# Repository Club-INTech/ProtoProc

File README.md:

# ProtoProc #

## Equipe: ##
- Dédé Belnet
- Martial Costantini
- Pierre-François Gimenez

# Projet: #
Concevoir et construire une console de jeu avec des portes logiques.

## Etapes ##
- concevoir un processeur RISC
- le réaliser électroniquement
- écrire un assembleur
- écrire un compilateur (?)
- écrire un jeu
- intégrer des éléments extérieurs (écran, manette)
- jouer

## Constituant d'un processeur ##
- ALU (unité arithmétique et logique)
- Register file
- Séquenceur
- Horloge
- Contrôleur mémoire
- Contrôleur d'interruption
- MMU

A se répartir.

## Eléments à choisir ##
- Combien de bits? (bits effectivement utilisés + bits de redondance)
- Quels adressages disponibles?
- Jeu d'instruction? (voir plus bas)
- Mode idle?
- Timer? Compteur?

### Proposition ###
- 3 bits (données)
- 8 registres accessibles: ACC1, ACC2, SP (accessible?), flags (zero, sign, carry) (accessible?), index high, index low, E/S 1 (ou seulement entrée), E/S 2 (ou seulement sortie). Registre nul? (utile pour comparaison à zéro et initialisation)
- adressage sur 15 bits immédiats (cf largeur du bus de la mémoire ram de RS)
- adresse sur 15 bits immédiats + 6 bits provenant des deux registres d'index (une adresse du genre 1400 + INDEX)

## Matériel utilisé ##
- transistor
- portes logiques
- décodeur ?
- bascule ?
- (dé)multiplexeur ?
- eeprom ? (mémoire programme et microcode) (utiliser communication parallèle: http://fr.rs-online.com/web/p/memoires-eeprom/0394504/)
- ram ? (mémoire données et mémoire de la carte graphique. Y'a pas de SDRAM traversant chez RS mais y'a du SRAM: http://fr.rs-online.com/web/p/memoires-sram/0538148/)

L'avantage avec un processeur lent, c'est que les temps d'accès mémoire se font en un tic d'horloge...

## Jeu d'instructions ##
Si on veut un jeu rapide, il ne faut pas se contenter de quelques instructions mais ajouter des instructions assez haut niveau.
Il y a deux sortes d'instructions: les câblés (inaltérables) et les micro-codés (programmable).
Les câblés sont plus rapides que les micro-codés, mais consomment beaucoup de portes logiques.

### Instructions câblée monocycle ###
- mov
- Instructions logiques et arithmétiques sur deux registres
- Saut conditionnel (se base sur les flags)
- Saut inconditionnel
- load/store
- nop

### Instructions microcodées à voir selon le jeu. ###
- Pile ? (push, pop, call, ret)
- load/store avec index?
- Echange du contenu de deux registres ?
- Comparaison suivi d'un saut ?
- Instructions sur des booléens ?
- Instructions mémoire-registre ?
- Une instruction de nop'ification qui permettrait de supprimer des branches et de faciliter le travail du pipeline.

Exemple, au lieu de:

```
#!Assembleur

    cmp A, 0
    jz Label1 // (saute si A == 0)
    mov B, 3
    mov A, 6
    jmp Label2
Label1:
    mov B, 9
    mov C, 4
Label2:
```

On aurait:

```
#!Assembleur

    cmp A, 0
    nopz 3 // (si A == 0, ignore les trois prochaines instructions)
    mov B, 3
    mov A, 6
    nop 2  // (ignore les deux prochaines instructions)
    mov B, 9
    mov C, 4
```

On perd du temps (les instructions ignorées durent un cycle chacune) mais cela retire en embranchement. Pour les branchements pour lesquels la nopification est impossible (label en arrière ou trop de code à noper), je rappelle qu'il faut toujours ajouter des nops après le branchement afin de ne pas exécuter les instructions en aval.

```
#!Assembleur

    cmp A, 0
    jz Label1 // saute si A == 0
    nop
    nop
    nop
    (ABWABWA)
Label1:
    (ABWABWABWABWAAAA)
```

## Idées ##
- Un jeu d'instruction dynamique (qui change sans que le processeur ne s'éteigne)
- Il faudrait en plus du processeur et de sa mémoire, une carte son (pour jouer de la musique avec un floppy) et une carte graphique (qui transmet les informations de la mémoire à la matrice de led). Les fréquences de ces trois systèmes ne sont pas forcément les mêmes.
- La carte graphique pourrait gérer une matrice de diode pour les images et des afficheurs 7 segments pour les nombres. Voire utiliser un petit écran LCD.

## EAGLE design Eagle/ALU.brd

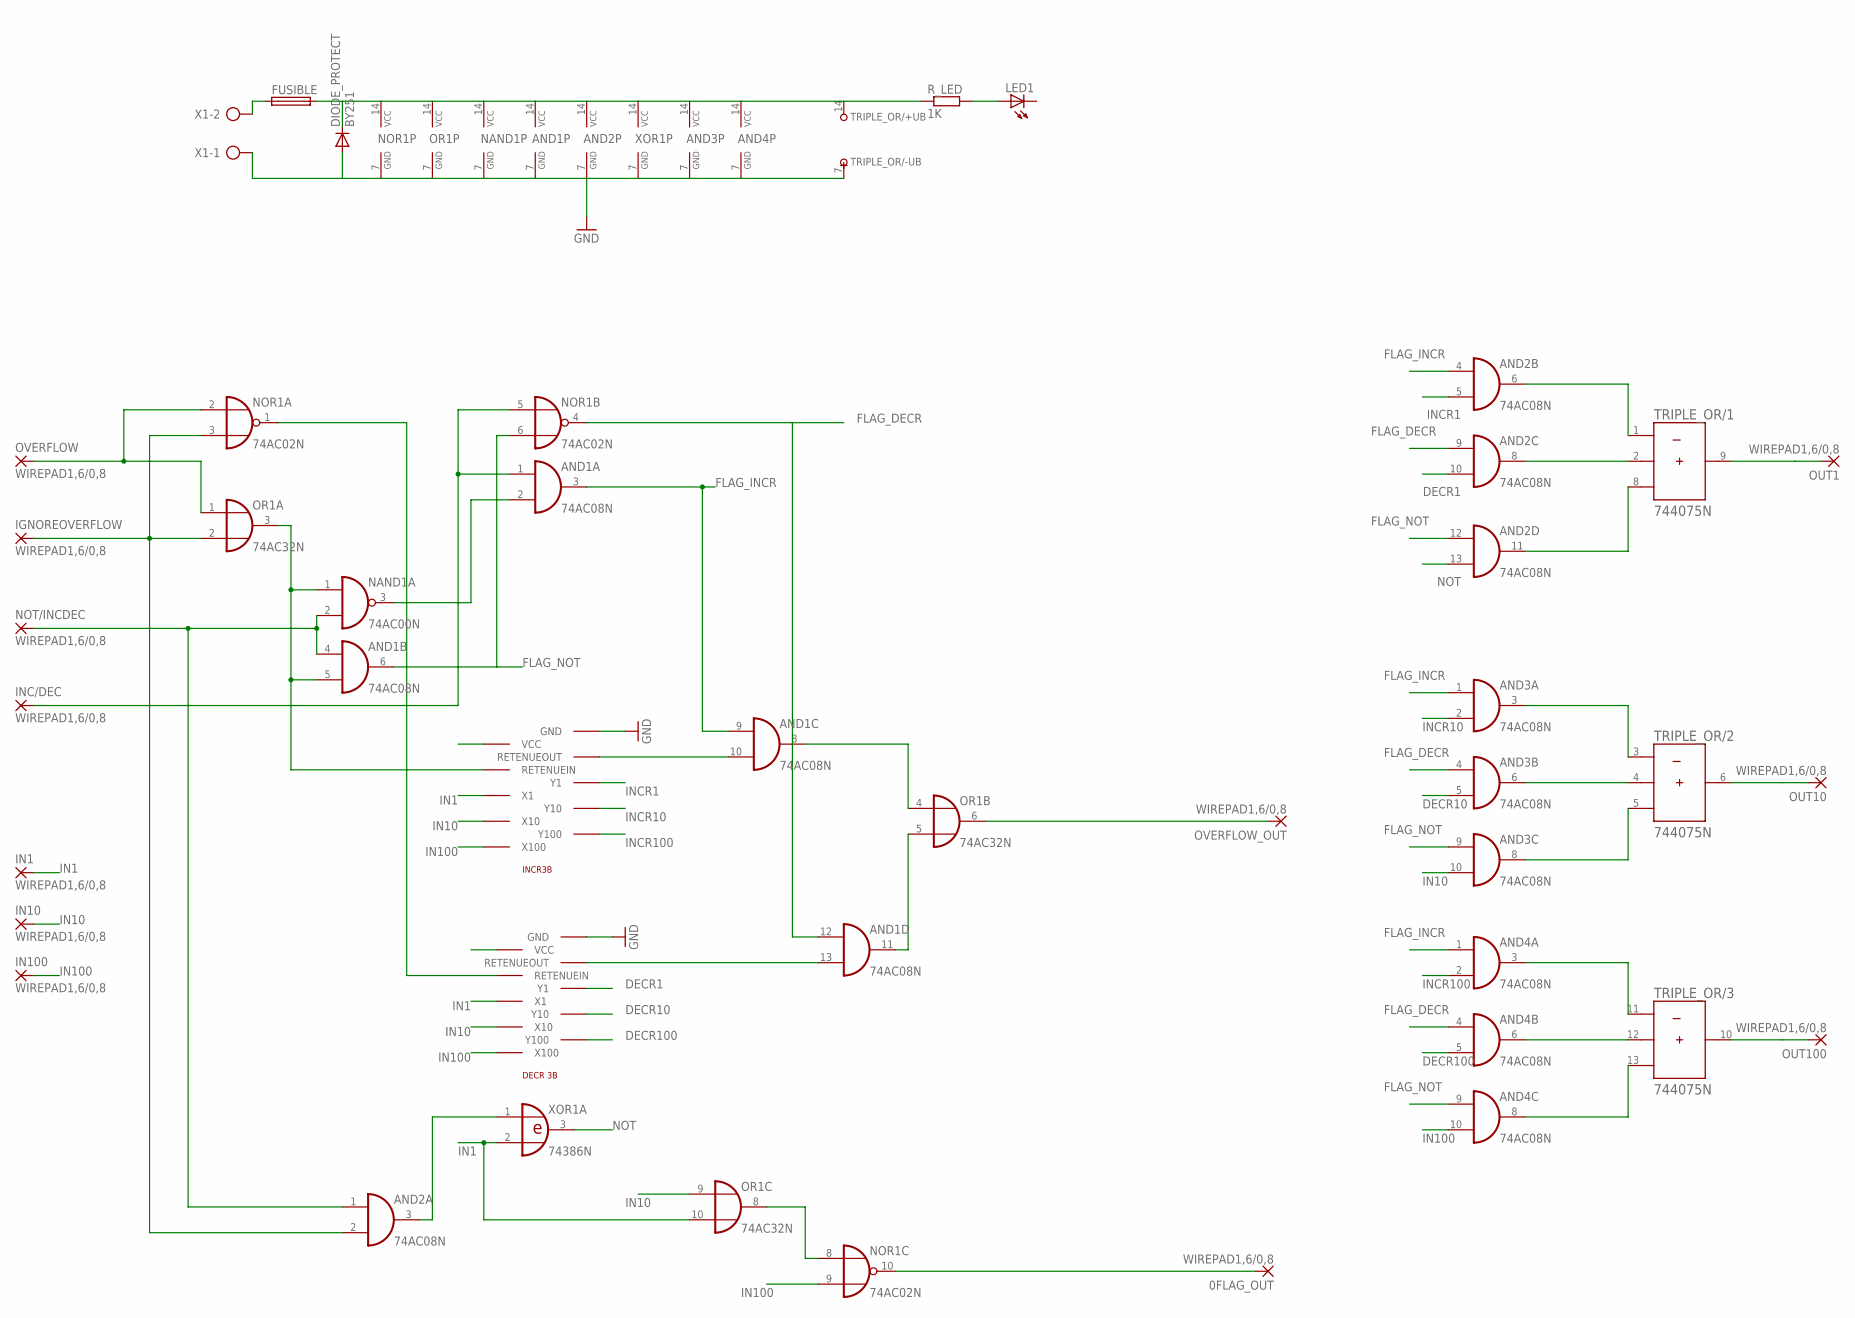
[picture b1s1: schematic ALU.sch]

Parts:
0FLAG_OUT: WIREPAD1,6/0,8; 1,6/0,8
AND1, AND2, AND3, AND4: 74AC08N; DIL14
DECR3B: DECR3B
DIODE_PROTECT: BY251; DO201-15
FUSIBLE: SH22,5A
IGNOREOVERFLOW: WIREPAD1,6/0,8; 1,6/0,8
IN1, IN10, IN100: WIREPAD1,6/0,8; 1,6/0,8
INC/DEC: WIREPAD1,6/0,8; 1,6/0,8
INCR3B: INCR3B
LED1: LEDSFH482; SFH482
NAND1: 74AC00N; DIL14
NOR1: 74AC02N; DIL14
NOT/INCDEC: WIREPAD1,6/0,8; 1,6/0,8
OR1: 74AC32N; DIL14
OUT1, OUT10, OUT100: WIREPAD1,6/0,8; 1,6/0,8
OVERFLOW: WIREPAD1,6/0,8; 1,6/0,8
OVERFLOW_OUT: WIREPAD1,6/0,8; 1,6/0,8
R_LED: 1K; 0207/10
TRIPLE_OR: 744075N; DIL14
X1: AK300/2
XOR1: 74386N; DIL14

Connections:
0FLAG_OUT: 0FLAG_OUT.1, NOR1.10 (O)
DECR1: AND2.10 (I1), DECR3B.Y1
DECR10: AND3.5 (I1), DECR3B.Y10
DECR100: AND4.5 (I1), DECR3B.Y100
FLAG_DECR: AND1.12 (I0), AND2.9 (I0), AND3.4 (I0), AND4.4 (I0), NOR1.4 (O)
FLAG_INCR: AND1.3 (O), AND1.9 (I0), AND2.4 (I0), AND3.1 (I0), AND4.1 (I0)
FLAG_NOT: AND1.6 (O), AND2.12 (I0), AND3.9 (I0), AND4.9 (I0), NOR1.6 (I1)
GND: AND1.7 (GND), AND2.7 (GND), AND3.7 (GND), AND4.7 (GND), DECR3B.GND, DIODE_PROTECT.A, INCR3B.GND, NAND1.7 (GND), NOR1.7 (GND), OR1.7 (GND), TRIPLE_OR.7 (-UB), X1.1, XOR1.7 (GND)
IN1: DECR3B.X1, IN1.1, INCR3B.X1, OR1.10 (I1), XOR1.2 (I1)
IN10: AND3.10 (I1), DECR3B.X10, IN10.1, INCR3B.X10, OR1.9 (I0)
IN100: AND4.10 (I1), DECR3B.X100, IN100.1, INCR3B.X100, NOR1.9 (I1)
INCR1: AND2.5 (I1), INCR3B.Y1
INCR10: AND3.2 (I1), INCR3B.Y10
INCR100: AND4.2 (I1), INCR3B.Y100
unnamed: NOR1.2 (I0), OR1.1 (I0), OVERFLOW.1
unnamed: AND2.6 (O), TRIPLE_OR.1 (A)
unnamed: AND1.2 (I1), NAND1.3 (O)
unnamed: AND1.1 (I0), INC/DEC.1, NOR1.5 (I0)
unnamed: AND1.4 (I0), AND2.1 (I0), NAND1.2 (I1), NOT/INCDEC.1
unnamed: AND1.5 (I1), INCR3B.RETENUEIN, NAND1.1 (I0), OR1.3 (O)
unnamed: AND2.8 (O), TRIPLE_OR.2 (B)
unnamed: DECR3B.RETENUEIN, NOR1.1 (O)
unnamed: AND1.8 (O), OR1.4 (I0)
unnamed: AND1.13 (I1), DECR3B.RETENUEOUT
unnamed: AND1.10 (I1), INCR3B.RETENUEOUT
unnamed: AND1.11 (O), OR1.5 (I1)
unnamed: OR1.6 (O), OVERFLOW_OUT.1
unnamed: AND2.2 (I1), IGNOREOVERFLOW.1, NOR1.3 (I1), OR1.2 (I1)
unnamed: AND2.3 (O), XOR1.1 (I0)
unnamed: NOR1.8 (I0), OR1.8 (O)
unnamed: AND2.11 (O), TRIPLE_OR.8 (C)
unnamed: FUSIBLE.1, X1.2
unnamed: LED1.A, R_LED.2
unnamed: AND3.3 (O), TRIPLE_OR.3 (A)
unnamed: AND3.6 (O), TRIPLE_OR.4 (B)
unnamed: AND3.8 (O), TRIPLE_OR.5 (C)
unnamed: AND4.3 (O), TRIPLE_OR.11 (A)
unnamed: AND4.6 (O), TRIPLE_OR.12 (B)
unnamed: AND4.8 (O), TRIPLE_OR.13 (C)
NOT: AND2.13 (I1), XOR1.3 (O)
OUT1: OUT1.1, TRIPLE_OR.9 (Y)
OUT10: OUT10.1, TRIPLE_OR.6 (Y)
OUT100: OUT100.1, TRIPLE_OR.10 (Y)
VCC: AND1.14 (VCC), AND2.14 (VCC), AND3.14 (VCC), AND4.14 (VCC), DECR3B.VCC, DIODE_PROTECT.C, FUSIBLE.2, INCR3B.VCC, NAND1.14 (VCC), NOR1.14 (VCC), OR1.14 (VCC), R_LED.1, TRIPLE_OR.14 (+UB), XOR1.14 (VCC)

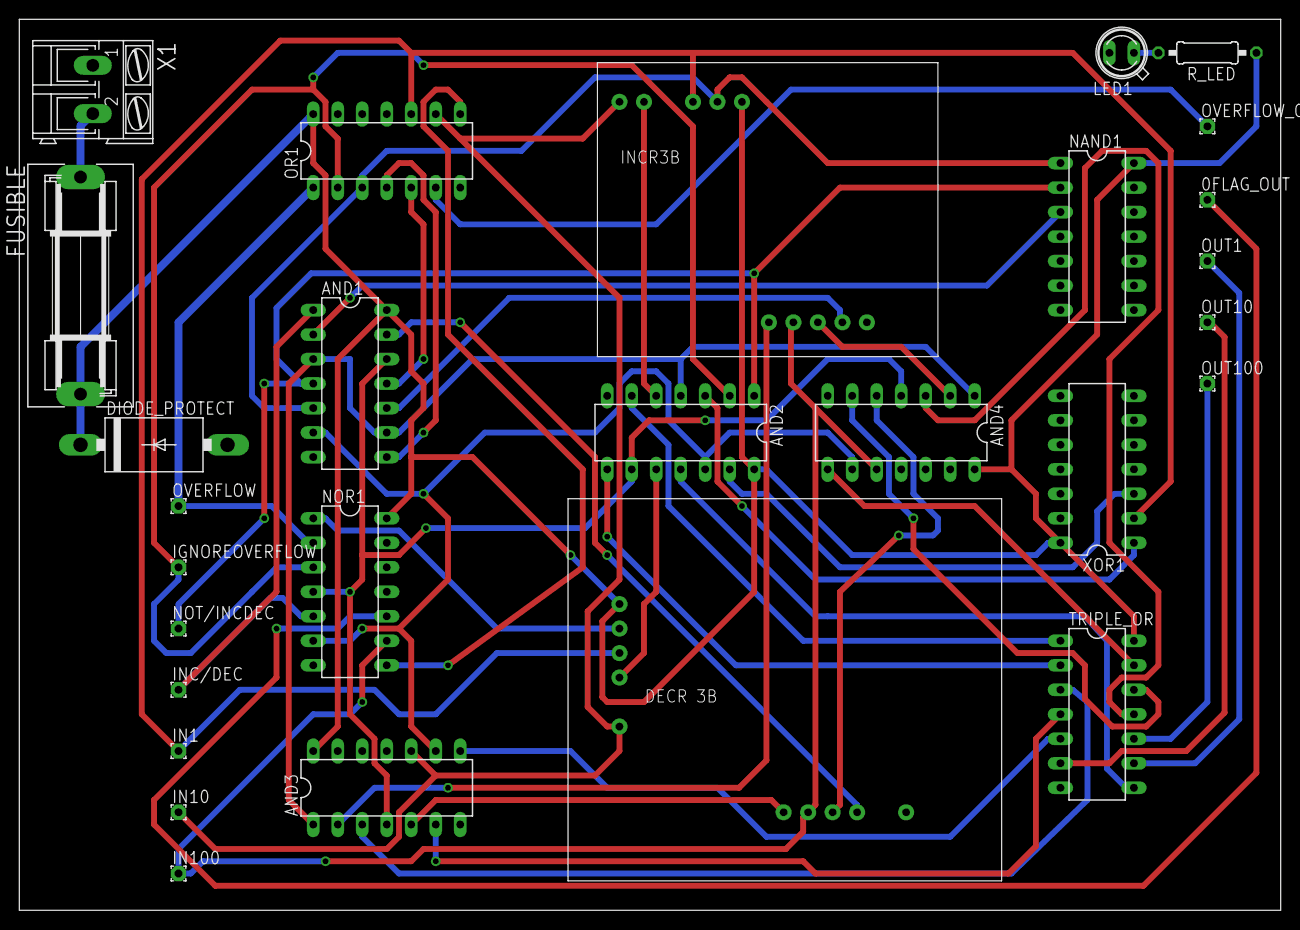
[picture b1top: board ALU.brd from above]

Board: 2 copper layers, 130.8 x 92.4 mm, 28 parts (0 on the bottom side), 44 nets.

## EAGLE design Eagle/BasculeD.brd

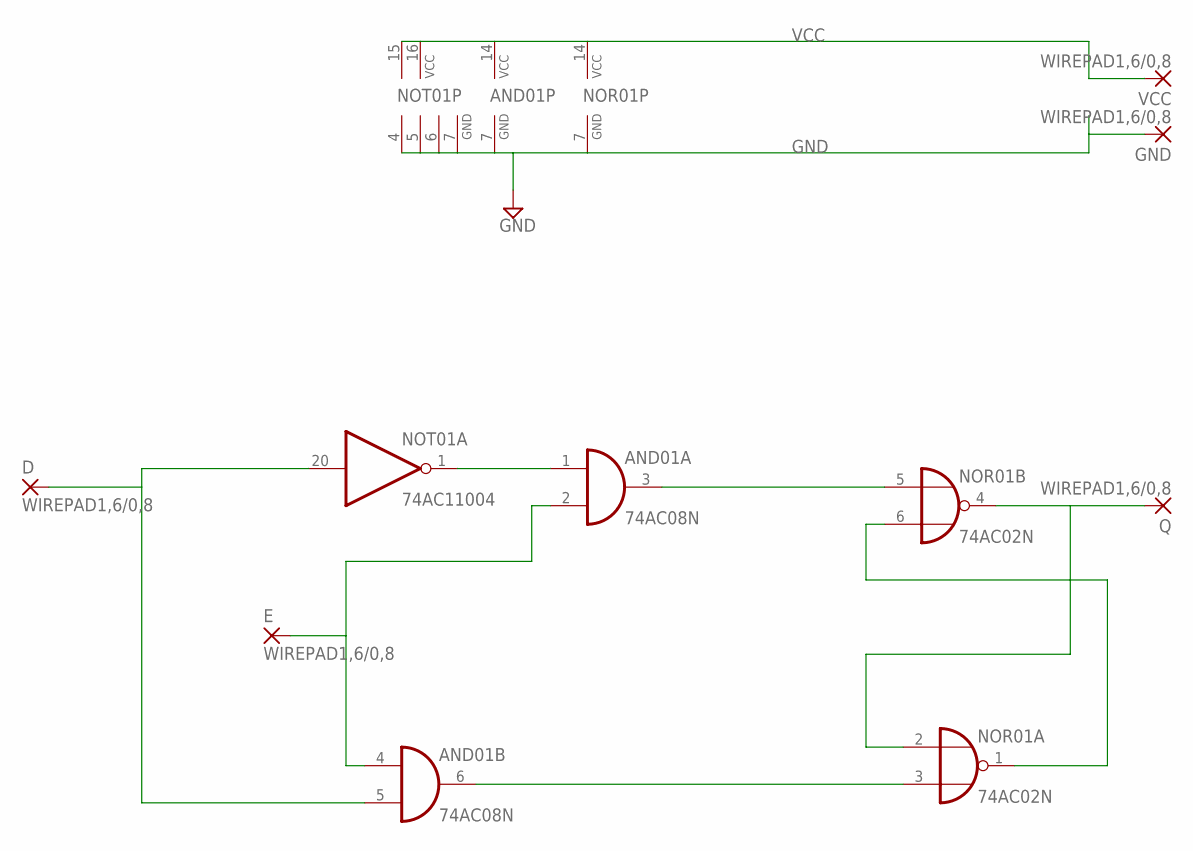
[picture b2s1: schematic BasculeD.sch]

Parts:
AND01: 74AC08N; DIL14
D: WIREPAD1,6/0,8; 1,6/0,8
E: WIREPAD1,6/0,8; 1,6/0,8
GND: WIREPAD1,6/0,8; 1,6/0,8
NOR01: 74AC02N; DIL14
NOT01: 74AC11004; DIL20
Q: WIREPAD1,6/0,8; 1,6/0,8
VCC: WIREPAD1,6/0,8; 1,6/0,8

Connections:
GND: AND01.7 (GND), GND.1, NOR01.7 (GND), NOT01.4 (GND), NOT01.5 (GND), NOT01.6 (GND), NOT01.7 (GND)
unnamed: AND01.1 (I0), NOT01.1 (O)
unnamed: AND01.3 (O), NOR01.5 (I0)
unnamed: NOR01.1 (O), NOR01.6 (I1)
unnamed: AND01.6 (O), NOR01.3 (I1)
unnamed: AND01.2 (I1), AND01.4 (I0), E.1
unnamed: AND01.5 (I1), D.1, NOT01.20 (I)
NOR01: NOR01.2 (I0), NOR01.4 (O), Q.1
VCC: AND01.14 (VCC), NOR01.14 (VCC), NOT01.15 (VCC), NOT01.16 (VCC), VCC.1

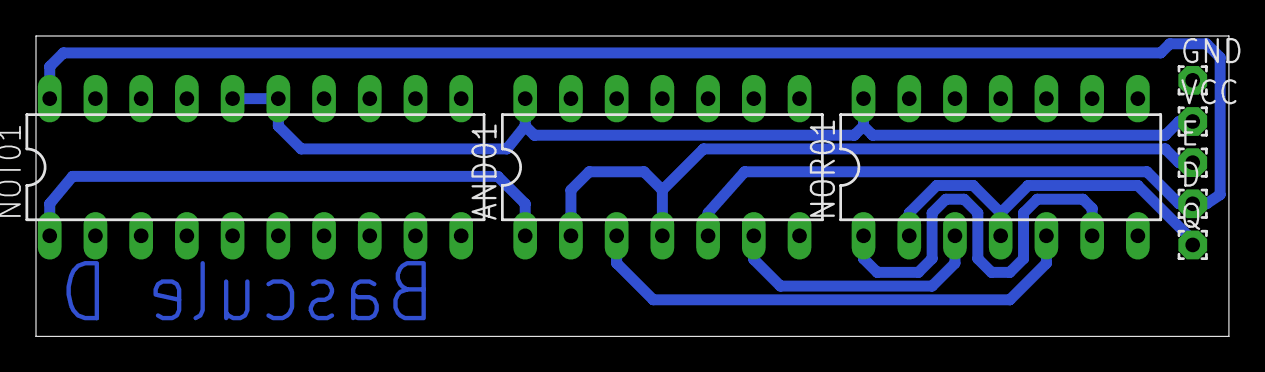
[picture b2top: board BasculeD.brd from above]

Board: 2 copper layers, 66.3 x 16.7 mm, 8 parts (0 on the bottom side), 9 nets.

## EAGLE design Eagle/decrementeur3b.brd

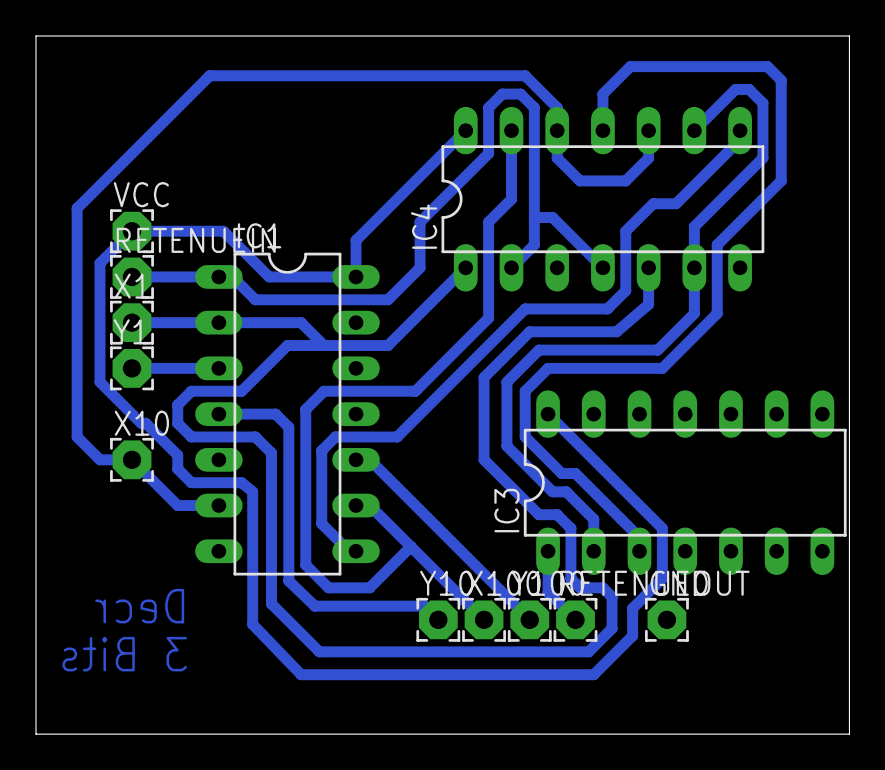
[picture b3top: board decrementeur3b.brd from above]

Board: 2 copper layers, 45.2 x 38.8 mm, 13 parts (0 on the bottom side), 13 nets.

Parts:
GND: WIREPAD2,15/1,0; 2,15/1,0
IC1: 74HC266N; DIL14
IC3: 74AC02N; DIL14
IC4: 74AC32N; DIL14
RETENUEIN: WIREPAD2,15/1,0; 2,15/1,0
RETENUEOUT: WIREPAD2,15/1,0; 2,15/1,0
VCC: WIREPAD2,15/1,0; 2,15/1,0
X1, X10, X100: WIREPAD2,15/1,0; 2,15/1,0
Y1, Y10, Y100: WIREPAD2,15/1,0; 2,15/1,0

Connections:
GND: GND.1, IC1.7, IC3.7, IC4.7
unnamed: IC1.2, IC4.1, IC4.5, X1.1
unnamed: IC1.1, IC4.2, IC4.4, RETENUEIN.1
unnamed: IC1.3, Y1.1
unnamed: IC3.2, IC4.6, IC4.9
unnamed: IC1.8, IC4.8
unnamed: IC1.9, IC4.13, X100.1
unnamed: IC1.6, IC4.10, IC4.12, X10.1
unnamed: IC1.10, Y100.1
unnamed: IC1.4, Y10.1
unnamed: IC3.3, IC4.11
unnamed: IC3.1, RETENUEOUT.1
VCC: IC1.14, IC3.14, IC4.14, VCC.1

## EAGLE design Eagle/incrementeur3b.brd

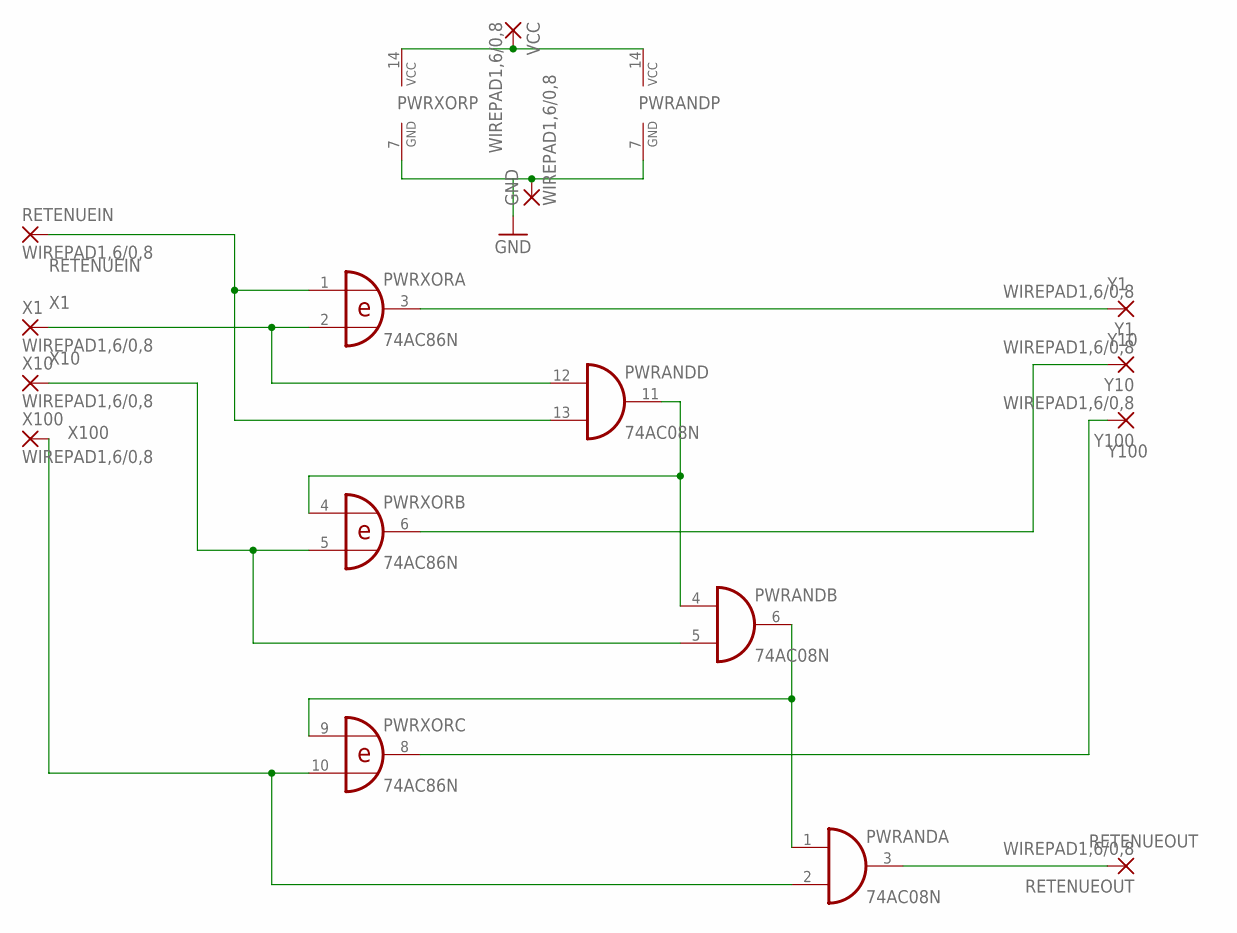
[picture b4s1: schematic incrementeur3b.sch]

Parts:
GND: WIREPAD1,6/0,8; 1,6/0,8
PWRAND: 74AC08N; DIL14
PWRXOR: 74AC86N; DIL14
RETENUEIN: WIREPAD1,6/0,8; 1,6/0,8
RETENUEOUT: WIREPAD1,6/0,8; 1,6/0,8
VCC: WIREPAD1,6/0,8; 1,6/0,8
X1, X10, X100: WIREPAD1,6/0,8; 1,6/0,8
Y1, Y10, Y100: WIREPAD1,6/0,8; 1,6/0,8

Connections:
GND: GND.1, PWRAND.7 (GND), PWRXOR.7 (GND)
unnamed: PWRAND.14 (VCC), PWRXOR.14 (VCC), VCC.1
unnamed: PWRAND.4 (I0), PWRAND.11 (O), PWRXOR.4 (I0)
unnamed: PWRAND.1 (I0), PWRAND.6 (O), PWRXOR.9 (I0)
RETENUEIN: PWRAND.13 (I1), PWRXOR.1 (I0), RETENUEIN.1
RETENUEOUT: PWRAND.3 (O), RETENUEOUT.1
X1: PWRAND.12 (I0), PWRXOR.2 (I1), X1.1
X10: PWRAND.5 (I1), PWRXOR.5 (I1), X10.1
X100: PWRAND.2 (I1), PWRXOR.10 (I1), X100.1
Y1: PWRXOR.3 (O), Y1.1
Y10: PWRXOR.6 (O), Y10.1
Y100: PWRXOR.8 (O), Y100.1

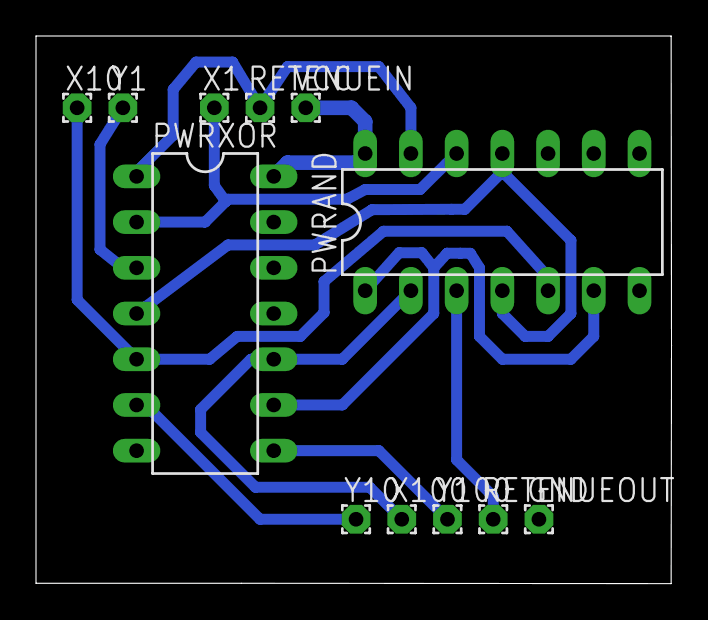
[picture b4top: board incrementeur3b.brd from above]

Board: 2 copper layers, 35.3 x 30.4 mm, 12 parts (0 on the bottom side), 12 nets.

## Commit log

2014-06-10 Initial commit with contributors
2014-06-10 contributors.txt edited online with Bitbucket
2014-06-11 README.md edited online with Bitbucket
2014-06-21 Circuits écrits avec logisim
2014-11-24 Projet C du jeu Tron
2014-11-24 Tron en assembleur (en cours)
2015-01-05 Code assembleur écrit
2015-01-08 Plus d'info sur le langage
2015-01-08 Documentation
2015-01-09 Incrémenteur et décrémenteur
2015-01-09 gitignore
2015-01-09 Optimisation de l'alu
2015-03-08 Debug des problèmes de nommage
2015-03-08 proprification plus avancee
2015-03-08 Doc, suppression de vieux trucs
2015-03-09 Debut de l'IDE pour le dev du code de tron. La coloration syntaxique marche pour les mnémoniques et les chiffres
2015-03-09 IDE terminé! coloration syntaxique complete, et numerotation de lignes. Plus qu'a faire le code d'assemblage et la machine virtuelle xD
2015-03-18 Les .sch et .brd de l'ALU, plus quelques modifs de la partie logique
2015-03-18 Retrait de toutes les versions inutiles des .sch et des .brd
2015-04-06 UI changes
2015-04-07 Code de benchmarks pour l'ALU
2015-04-07 Le code pour les benchmarks de l'ALU sur Arduino 328p. Non testé
2015-04-08 Modification de la forme de la monoinstruction
2015-04-09 board Bascule D
2015-04-10 finalisation du routage bascule D
2017-11-03 Create LICENSE
